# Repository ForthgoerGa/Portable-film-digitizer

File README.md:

# Portable Multi-Format Film Digitization System

ECE 445 coursework design project repository for hardware/firmware/software development and lab notebook tracking.

Results:

## System Block Diagram
This block diagram shows the general system design and how the power subsystem, control unit, and imaging subsystem are connected.

## Project Goal
Build a portable, battery-powered film digitizer that supports:
- 35mm negatives/slides (transmissive)
- 120 medium format film (transmissive)
- Instax Mini prints (reflective)

The system captures a raw frame, uploads via Wi-Fi, performs cloud processing (negative inversion + enhancement), and returns a social-media-ready image.

## Problem
Current film digitization workflows are either:
- expensive and slow (professional scanners),
- fast but complex and non-portable (DSLR scanning rigs),
- or outsourced with long turnaround times (lab services).

This project targets a one-click workflow with fast turnaround and practical portability.

## Solution Overview
An STM32-based control system coordinates:
- dual-mode illumination (backlight for transmissive film, angled front light for reflective media),
- high-resolution sensor capture,
- network upload to cloud backend,
- return of processed output to a mobile device.

## Major Subsystems
1. **Power Supply and Management (PCB)**  
   Li-Ion battery pack, charging/protection (BMS), regulated rails for logic and LEDs.
2. **MCU and Control (STM32F4/H7)**  
   UI handling, capture sequencing, sensor interface, and network orchestration.
3. **Dual-Mode Illumination**  
   High-CRI transmissive array + glare-controlled reflective array, PWM-controlled.
4. **Cloud Processing Pipeline (Python)**  
   Negative inversion (orange mask handling), denoising, sharpening, and API response.

## Optical Stack (Current Plan)
- Sensor: Raspberry Pi HQ Camera (IMX477)
- Lens: 25mm f/1.4 C-mount lens
- Extension: 10mm C-mount tube for macro working distance (~8.5 cm)

## Success Criteria
- Resolution: at least `3840 x 2160` output.
- Speed: under `15 seconds` from capture press to phone delivery (stable network).
- Versatility: works with 35mm, 120, and Instax Mini.
- Portability: under `30 cm x 20 cm x 15 cm`, under `1.5 kg`.
- Battery: at least `360 shots` (~10 rolls) per charge.

## Repository Layout
```text
hardware/              PCB + mechanical design files
firmware/              STM32 firmware and drivers
software/              Cloud/image-processing code and APIs
docs/                  Specs, architecture, plans, reports
lab-notebook/          Dated engineering logs
```

## Lab Notebook Workflow
1. Add one file per workday in `lab-notebook/` using `YYYY-MM-DD.md`.
2. Record decisions, measurements, failures, and next steps.
3. Include links to commits, issues, and test data where possible.
4. Use `lab-notebook/TEMPLATE.md` for consistency.

## Quick Start (Local)
```powershell
git init -b main
git add .
git commit -m "Initial project scaffold"
```

## Running the Software

### Web Inspection Server (PC)
Runs the FastAPI server with the web UI for scan control and image review:
```bash
cd software && python server.py
# FastAPI at http://localhost:8000, web UI at http://localhost:8000/web/
```

### Raspberry Pi Camera Server
Streams a live MJPEG preview, triggers captures, and forwards to the PC pipeline:
```bash
# On the Raspberry Pi:
python3 software/rpi_camera_server.py [--port 8080] [--button-pin 17] [--pc-host <PC_IP>]
# Web UI at http://<pi-ip>:8080/
```

### Agentic Post-Processing Pipeline
Runs the Gemini-powered agent loop (classify → process → evaluate → refine):
```bash
cd Agentic_Post_Processing
python orchestrator.py --input-dir data --output-dir output --max-iter 2
```
Requires a `.env` file with `GEMINI_API_KEY` (see `.env.example`). Falls back to heuristics automatically if the key is absent.

### Raw Negative Pipeline (direct)
```bash
python software/processing/negative_pipeline.py \
  --tiles-dir "Image_integration&Post_Processing/Negative_example/norway_split_40_overlap" \
  --output-dir "Image_integration&Post_Processing/output_demo" \
  --wb-clip-percent 0.5
```

## GitHub Setup
See `docs/github-setup.md` for:
- creating the remote repo,
- pushing `main`,
- inviting collaborator `Allannn-sudo`.

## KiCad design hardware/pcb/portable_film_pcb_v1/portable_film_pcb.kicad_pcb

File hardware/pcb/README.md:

# PCB

Place PCB design files here.

## Suggested structure
- `schematics/`
- `layout/`
- `bom/`
- `gerbers/`
- `test-results/`

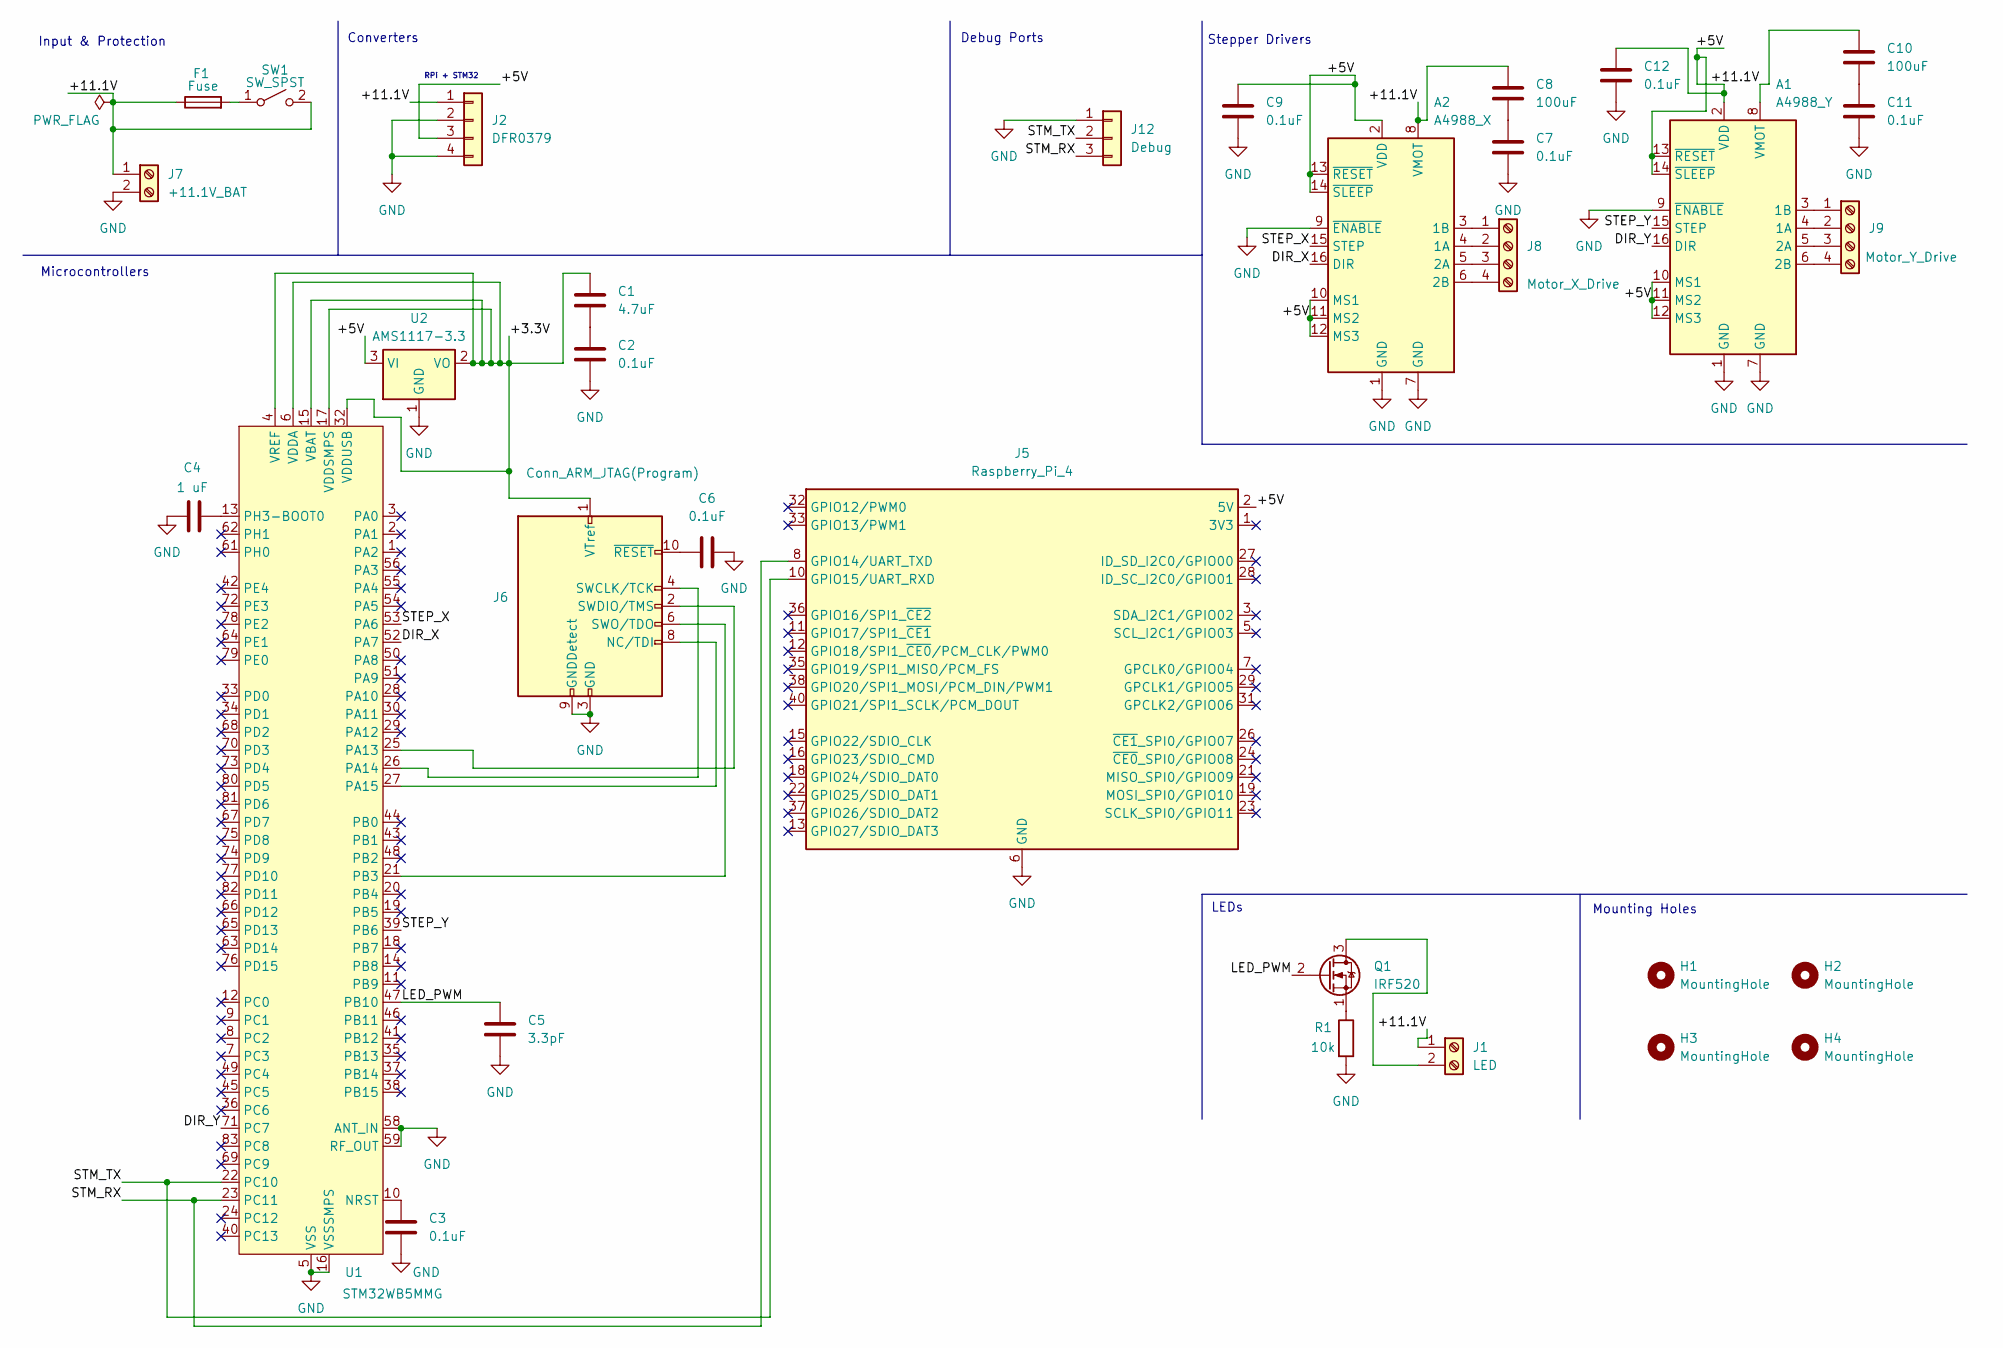
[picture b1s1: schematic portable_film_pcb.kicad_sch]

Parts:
A1: A4988_Y; Pololu_Breakout-16_15.2x20.3mm
A2: A4988_X; Pololu_Breakout-16_15.2x20.3mm
C1: 4.7uF; CP_Radial_D5.0mm_P2.00mm
C2, C3, C6, C7, C9, C11, C12: 0.1uF; C_Disc_D5.0mm_W2.5mm_P2.50mm
C4: 1 uF; C_Disc_D5.0mm_W2.5mm_P5.00mm
C5: 3.3pF; C_0201_0603Metric
C8, C10: 100uF; CP_Radial_D8.0mm_P3.50mm
F1: Fuse; FuseHolder_Blade_ATO_Littelfuse_FLR_178.6165
H1, H2, H3, H4: MountingHole; MountingHole_3.2mm_M3
J1: LED; TerminalBlock_Phoenix_PT-1,5-2-3.5-H_1x02_P3.50mm_Horizontal
J2: DFR0379; TerminalBlock_Phoenix_MKDS-1,5-4-5.08_1x04_P5.08mm_Horizont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
J5: Raspberry_Pi_4; PinSocket_2x20_P2.54mm_Vertical
J6: Conn_ARM_JTAG(Program); PinHeader_2x05_P1.27mm_Vertical
J7: +11.1V_BAT; TerminalBlock_Phoenix_PT-1,5-2-3.5-H_1x02_P3.50mm_Horizontal
J8: Motor_X_Drive; TerminalBlock_Phoenix_MPT-0,5-4-2.54_1x04_P2.54mm_Horizontal
J9: Motor_Y_Drive; TerminalBlock_Phoenix_MPT-0,5-4-2.54_1x04_P2.54mm_Horizontal
J12: Debug; PinSocket_1x03_P2.54mm_Vertical
Q1: IRF520; TO-92_Inline
R1: 10k; R_Axial_DIN0207_L6.3mm_D2.5mm_P7.62mm_Horizontal
SW1: SW_SPST; TerminalBlock_Phoenix_MKDS-1,5-2-5.08_1x02_P5.08mm_Horizont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
U1: STM32WB5MMG; ST-SiP-LGA-86-11x7.3mm
U2: AMS1117-3.3; SOT-223-3_TabPin2

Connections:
/+3.3V: C1.1, J6.1 (VTref), U1.4 (VREF), U1.6 (VDDA), U1.15 (VBAT), U1.17 (VDDSMPS), U1.32 (VDDUSB), U2.2 (VO)
/+5V: A1.2 (VDD), A1.10 (MS1), A1.11 (MS2), A1.12 (MS3), A1.13 (~RESET), A1.14 (~SLEEP), A2.2 (VDD), A2.10 (MS1), A2.11 (MS2), A2.12 (MS3), A2.13 (~RESET), A2.14 (~SLEEP), C9.1, C12.1, J2.3, J5.2 (5V), J5.4 (5V), U2.3 (VI)
/+11.1V: A1.8 (VMOT), A2.8 (VMOT), C8.1, C10.1, F1.1, J1.1, J2.1, J7.1, SW1.2 (B)
/DIR_X: A2.16 (DIR), U1.52 (PA7)
/DIR_Y: A1.16 (DIR), U1.71 (PC7)
/LED_PWM: C5.1, Q1.2 (G), U1.47 (PB10)
/STEP_X: A2.15 (STEP), U1.53 (PA6)
/STEP_Y: A1.15 (STEP), U1.39 (PB6)
/STM_RX: J5.8 (GPIO14/UART_TXD), J12.3, U1.23 (PC11)
/STM_TX: J5.10 (GPIO15/UART_RXD), J12.2, U1.22 (PC10)
GND: A1.1 (GND), A1.7 (GND), A1.9 (~ENABLE), A2.1 (GND), A2.7 (GND), A2.9 (~ENABLE), C2.2, C3.2, C4.1, C5.2, C6.2, C7.2, C9.2, C11.2, C12.2, J2.2, J2.4, J5.6 (GND), J5.9 (GND), J5.14 (GND), J5.20 (GND), J5.25 (GND), J5.30 (GND), J5.34 (GND), J5.39 (GND), J6.3 (GND), J6.5 (GND), J6.9 (GNDDetect), J7.2, J12.1, R1.2, U1.5 (VSS), U1.16 (VSSSMPS), U1.31 (VSS), U1.57 (VSS), U1.58 (ANT_IN), U1.59 (RF_OUT), U1.60 (VSS), U1.84 (VSS), U1.86 (VSS), U2.1 (GND)
unnamed: A1.4 (1A), J9.2
unnamed: A1.3 (1B), J9.1
unnamed: A1.5 (2A), J9.3
unnamed: A1.6 (2B), J9.4
unnamed: A2.4 (1A), J8.2
unnamed: A2.3 (1B), J8.1
unnamed: A2.5 (2A), J8.3
unnamed: A2.6 (2B), J8.4
unnamed: C1.2, C2.1
unnamed: C7.1, C8.2
unnamed: C10.2, C11.1
unnamed: J1.2, Q1.3 (D)
unnamed: J6.8 (NC/TDI), U1.27 (PA15)
unnamed: J6.4 (SWCLK/TCK), U1.26 (PA14)
unnamed: J6.2 (SWDIO/TMS), U1.25 (PA13)
unnamed: J6.6 (SWO/TDO), U1.21 (PB3)
unnamed: C6.1, J6.10 (~RESET)
unnamed: Q1.1 (S), R1.1
unnamed: F1.2, SW1.1 (A)
unnamed: C3.1, U1.10 (NRST)
unnamed: C4.2, U1.13 (PH3-BOOT0)

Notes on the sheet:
LEDs
Converters
Stepper Drivers
Microcontrollers
Mounting Holes
Input & Protection
Debug Ports
RPi + STM32

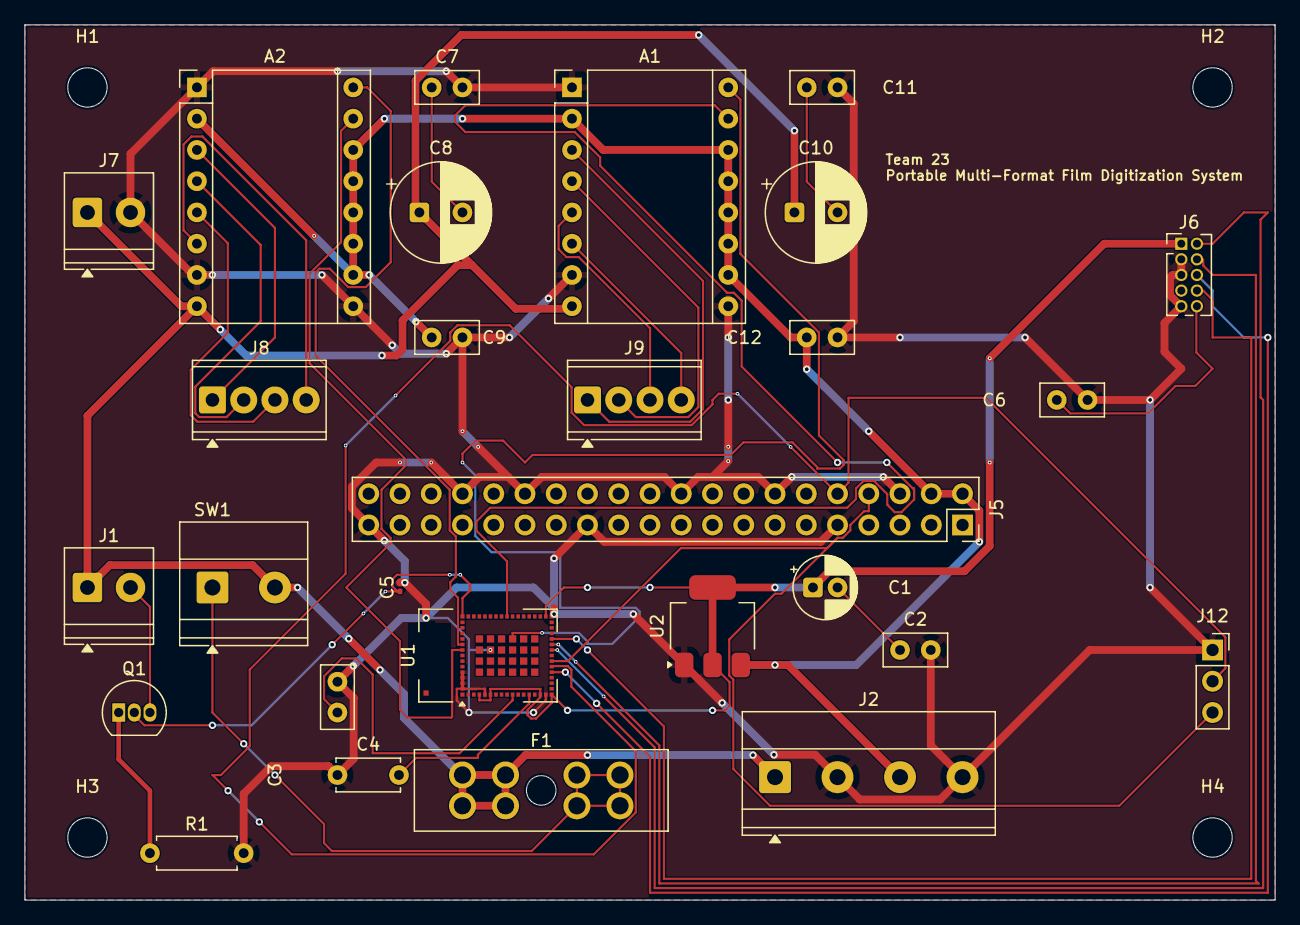
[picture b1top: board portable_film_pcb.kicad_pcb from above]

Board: 2 copper layers, 101.6 x 71.1 mm, 32 parts (0 on the bottom side), 32 nets.

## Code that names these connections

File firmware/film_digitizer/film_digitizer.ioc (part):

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Mcu.Name=STM32F401R(D-E)Tx
Mcu.Package=LQFP64
Mcu.UserName=STM32F401RETx
PA10.Mode=Asynchronous
PA10.Signal=USART1_RX
PA11.GPIOParameters=GPIO_Speed,GPIO_Label
PA11.GPIO_Label=DIR_Y_PIN
PA11.GPIO_Speed=GPIO_SPEED_FREQ_HIGH
PA11.Signal=GPIO_Output
PA13.GPIOParameters=GPIO_Label
PA13.GPIO_Label=TMS
PA13.Mode=Serial_Wire
PA13.Signal=SYS_JTMS-SWDIO
PA14.GPIOParameters=GPIO_Label
PA14.GPIO_Label=TCK
PA14.Mode=Serial_Wire
PA14.Signal=SYS_JTCK-SWCLK
PA2.GPIOParameters=GPIO_Speed,GPIO_PuPd,GPIO_Label,GPIO_Mode
PA2.GPIO_Label=USART_TX
PA2.GPIO_Mode=GPIO_MODE_AF_PP
PA2.GPIO_PuPd=GPIO_NOPULL
PA2.GPIO_Speed=GPIO_SPEED_FREQ_LOW
PA2.Mode=Asynchronous
PA2.Signal=USART2_TX
PA3.GPIOParameters=GPIO_Speed,GPIO_PuPd,GPIO_Label,GPIO_Mode
PA3.GPIO_Label=USART_RX
PA3.GPIO_Mode=GPIO_MODE_AF_PP
PA3.GPIO_PuPd=GPIO_NOPULL
PA3.GPIO_Speed=GPIO_SPEED_FREQ_LOW
PA3.Mode=Asynchronous
PA3.Signal=USART2_RX
PA5.GPIOParameters=GPIO_Speed,GPIO_PuPd,GPIO_Label,GPIO_Mode
PA5.GPIO_Label=LD2 [Green Led]
PA5.GPIO_Mode=GPIO_MODE_OUTPUT_PP
PA5.GPIO_PuPd=GPIO_NOPULL
PA5.GPIO_Speed=GPIO_SPEED_FREQ_LOW
PA5.Signal=GPIO_Output
PA6.Signal=S_TIM3_CH1
PA8.GPIOParameters=GPIO_Speed,GPIO_Label
PA8.GPIO_Label=STEP_X_PIN
PA8.GPIO_Speed=GPIO_SPEED_FREQ_VERY_HIGH
PA8.Signal=GPIO_Output
PA9.GPIOParameters=GPIO_Speed,GPIO_Label
PA9.GPIO_Label=DIR_X_PIN
PA9.GPIO_Speed=GPIO_SPEED_FREQ_VERY_HIGH
PA9.Signal=GPIO_Output
PB3.GPIOParameters=GPIO_Label
PB3.GPIO_Label=SWO
PB3.Signal=SYS_JTDO-SWO
PB6.Mode=Asynchronous
PB6.Signal=USART1_TX
PC13-ANTI_TAMP.GPIOParameters=GPIO_PuPd,GPIO_Label,GPIO_ModeDefaultEXTI
PC13-ANTI_TAMP.GPIO_Label=B1 [Blue PushButton]
PC13-ANTI_TAMP.GPIO_ModeDefaultEXTI=GPIO_MODE_IT_FALLING
PC13-ANTI_TAMP.GPIO_PuPd=GPIO_NOPULL
PC13-ANTI_TAMP.Signal=GPXTI13
PC14-OSC32_IN.Mode=LSE-External-Oscillator
PC14-OSC32_IN.Signal=RCC_OSC32_IN
PC15-OSC32_OUT.Mode=LSE-External-Oscillator
PC15-OSC32_OUT.Signal=RCC_OSC32_OUT
PC7.GPIOParameters=GPIO_Speed,GPIO_Label
PC7.GPIO_Label=STEP_Y_PIN
PC7.GPIO_Speed=GPIO_SPEED_FREQ_VERY_HIGH
PC7.Signal=GPIO_Output
PH0\ -\ OSC_IN.Mode=HSE-External-Clock-Source
PH0\ -\ OSC_IN.Signal=RCC_OSC_IN
PH1\ -\ OSC_OUT.Mode=HSE-External-Clock-Source
PH1\ -\ OSC_OUT.Signal=RCC_OSC_OUT
RCC.HSE_VALUE=8000000
RCC.SYSCLKFreq_VALUE=84000000
RCC.SYSCLKSource=RCC_SYSCLKSOURCE_PLLCLK
board=NUCLEO-F401RE
boardIOC=true

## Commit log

2026-02-10 Initial project scaffold and documentation
2026-02-10 Add GitHub bootstrap script and setup guide
2026-02-10 Add system block diagram to README intro
2026-02-25 Add portable_film_pcb_v1 KiCad project & gerbers
    Import new PCB design directory portable_film_pcb_v1: adds KiCad project files (.kicad_pcb, .kicad_sch, .kicad_pro, .kicad_prl, .kicad_dru), Gerber outputs and .gbrjob, PDF fabrication drawing, a lar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
2026-02-28 Update system block diagram image source
    Replaced local image with an external link for the system block diagram.
2026-02-28 added engineering notebook entry to new github repository
2026-03-08 RPI python control loop and mock integrations with serial interface and cloud endpoint
2026-03-08 Integrate film processing pipeline into web scan flow
2026-03-08 Add 40-tile negative sample dataset for integration demo
2026-03-09 Display tiled images and write processed result to s3
2026-03-09 entries from week of design review
2026-03-16 notebook entry for control plane dev
2026-03-20 experiments and metrics with AWS
2026-04-06 Measurements for motor motion profile
2026-04-18 Initial commit for stm32CubeIDE project
2026-04-18 Serial command interface
2026-04-19 serial control interface and motor controller experiments
2026-04-19 feat: added serial commands to web UI
2026-04-19 debug for serial port
2026-04-20 control loop
2026-04-20 2-axis motor control
2026-04-21 serial console
2026-04-21 Add RPi camera server with developer mode UI
    - MJPEG live stream, DNG+JPEG capture at ISO 100 / 1/20s, AWB fix after capture
    - Developer mode UI (/dev): frame role assignment (base/backlight/film), canvas
    ROI crop tool, per-run pipeline trigger with live log streaming
    - Pipeline stage diagram: 8 connected stages with collapsible thumbnails,
    large final result on completion, lightbox on click
    - Per-run timestamped output dirs (processed/run_YYYYMMDD_HHMMSS/) so previous
2026-04-21 Add gateway-backed model configuration
2026-04-21 Add optional GPT-5.2 decision escalation path
2026-04-21 Refine decision model into tiered GPT-5 routing
2026-04-21 Improve raw pipeline characterization and diagnostics
2026-04-21 Align decision tier defaults with measured stability
2026-04-21 Log decision tier usage in pipeline metadata
2026-04-22 raspberry pi gpio controller
2026-04-22 accel loop
2026-04-22 dual axis control
2026-04-22 working 2-axis controller
2026-04-22 added directional support
2026-04-22 camera server to view live feed in browser
2026-04-22 temp
2026-04-23 added S-scan mode with live preview
2026-04-23 major refactor to state machine and API server
2026-04-23 refactor
2026-04-23 removed mock libs
2026-04-23 fixed import bug
2026-04-23 Add raw pipeline, Pi camera integration, and physical negative processing
    - orchestrator.py: add process_raw_image() with bounded agent loop over
    flat-field/film-characterization/density-inversion/render-refinement;
    auto-route RAW inputs (.dng/.arw/etc.) and batch RAW directories;
    new --flat/--leader/--frame CLI args for single-frame mode
    - film_characterization.py: fix leader calibration fallback when
    D-max is implausibly high (>4.0); fall back to scene-based estimate
2026-04-23 manual test script
2026-04-23 file viewer
2026-04-23 fixed timeout error
2026-04-23 file explorer change
2026-04-23 Ignore local runtime outpus
2026-04-23 camera noop on error
2026-04-23 updated motor controller state machine
2026-04-23 Add web integration framework draft
2026-04-23 working scan UI and CLI
2026-04-23 working scan pattern: need to configure params in config.py
2026-04-23 Align Phase 1 web framework orchestration
2026-04-23 Fix Stage 2 and 3 Lab color contract
2026-04-24 Add calibrated Pi scan stitching workflow
2026-04-24 leo: updated UI functionality and integration with post pipelin
2026-04-24 PC-server
2026-04-25 4/24 EOD -- working breadboard scan and stitching
2026-04-25 Integrate Pi scan workflow and RAW processing
2026-04-25 calibration data
2026-04-25 light control library
2026-04-26 change stiching from Pi side to PC side
2026-04-27 Package deployment config and processing workflow
2026-04-27 final week of work, integrations
2026-04-27 Enhance README with images and system block diagram
    Added images to README for better visualization.
2026-04-27 Fix formatting in README.md
2026-04-27 Enhance README with project introduction
    Added a new line to introduce the project more clearly.
2026-04-27 Remove duplicate project description from README
2026-04-27 Add images to README for project visualization
    Added images to README for better visualization.
2026-04-27 Replace project images in README
    Updated the project images in the README file.
2026-04-27 Add results section to README
    Added results section with an image to README.
2026-04-30 final demo and presentation
2026-05-01 Create template for lab notebook entries
    Added a structured template for lab notebook entries.
2026-05-01 Create template for lab notebook entry
    Added structure for lab notebook entry with sections for objectives, work completed, measurements, issues, decisions, next steps, and time spent.
2026-05-01 Initialize lab notebook entry template
    Added structure for lab notebook entry with sections for objectives, work completed, measurements, issues, decisions, next steps, and time spent.
2026-05-01 Create template for lab notebook entry
    Added a structured template for lab notebook entries.
2026-05-01 Create template for lab notebook entry
    Added structured template for lab notebook entry.
2026-05-01 Create template for lab notebook entry
    Added structure for lab notebook entry with sections.
2026-05-01 Rename Block_Diagram.png to Block_Diagram_old.png
2026-05-01 Add old motion system requirements and block diagram
2026-05-06 add notebook file
2026-05-06 Revise lab notebook for 2026-02-17
    Updated the lab notebook with objectives, work completed, decisions made, and next steps for the project.
2026-05-06 Revise lab notebook entry for 2026-02-24
    Updated lab notebook entry with new date and details.
2026-05-06 Rename 2026-02-20.md to 2026-02-24.md
2026-05-06 Revise lab notebook entry for 2026-03-05
    Updated lab notebook entry for March 5, 2026, detailing design decisions and changes in motor choice.
2026-05-06 Revise lab notebook for March 12, 2026
    Updated the lab notebook entry for March 12, 2026, including objectives, completed work, and decisions made.
2026-05-06 Revise lab notebook entry for March 26, 2026
    Updated lab notebook entry for March 26, 2026, detailing objectives, work completed, measurements, issues, decisions, and next steps.
2026-05-06 Update lab notebook with debugging notes
    Added debugging notes regarding motor performance and adjustments made to eliminate skipping steps.
2026-05-06 Document AXI Slave Interface integration details
    Added details about AXI Slave Interface integration, including objectives, work completed, and code snippet for the AXI Register Write Handler.
2026-05-06 Update lab notebook entry for 2026-04-09
    Removed AXI Register Write Handler code snippet and added an image.
2026-05-06 Fix HTML encoding in lab notebook entry
2026-05-06 Revise lab notebook for April 16, 2026
    Updated lab notebook entry for April 16, 2026, including objectives, work completed, measurements, issues, decisions, and next steps.
2026-05-06 Revise lab notebook for April 24, 2026
    Updated lab notebook entry for April 24, 2026, to reflect completed work, objectives, and decisions made.
2026-05-06 Update date in lab notebook entry
2026-05-07 Enhance README with project updates and images
    Added in images taken through development progress
2026-05-07 add report
2026-05-07 add slides
